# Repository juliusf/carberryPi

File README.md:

carberryPi
==========

1. Introduction
----------------

This project aims to build a linux-car pc based on the raspberry pi minicomputer.

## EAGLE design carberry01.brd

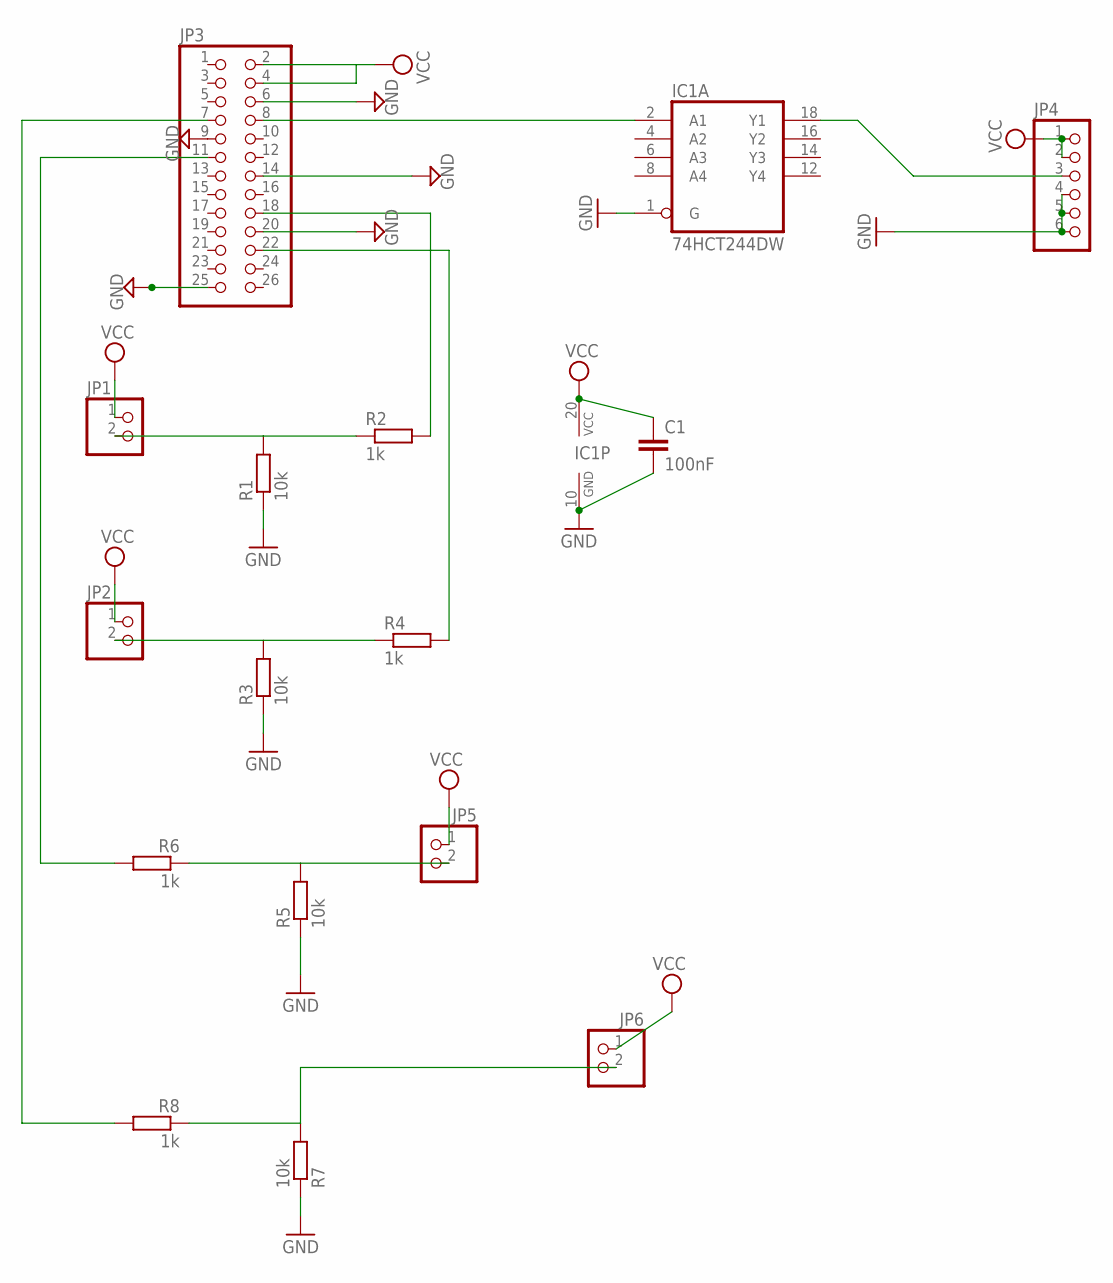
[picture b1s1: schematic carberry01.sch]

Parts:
C1: 100nF; C0603K
IC1: 74HCT244DW; SO20W
JP1, JP2, JP5, JP6: PINHD-1X2; 1X02
JP3: PINHD-2X13; 2X13
JP4: PINHD-1X6; 1X06
R1, R3, R5, R7: 10k; R0603
R2, R4, R6, R8: 1k; R0603

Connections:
GND: C1.2, IC1.1 (G), IC1.10 (GND), JP3.6, JP3.9, JP3.14, JP3.20, JP3.25, JP4.4, JP4.5, JP4.6, R1.1, R3.1, R5.1, R7.1
unnamed: IC1.18 (Y1), JP4.3
unnamed: JP1.2, R1.2, R2.1
unnamed: IC1.2 (A1), JP3.8
unnamed: JP2.2, R3.2, R4.1
unnamed: JP5.2, R5.2, R6.1
unnamed: JP6.2, R7.2, R8.1
unnamed: JP3.18, R2.2
unnamed: JP3.22, R4.2
unnamed: JP3.11, R6.2
unnamed: JP3.7, R8.2
VCC: C1.1, IC1.20 (VCC), JP1.1, JP2.1, JP3.2, JP3.4, JP4.1, JP4.2, JP5.1, JP6.1

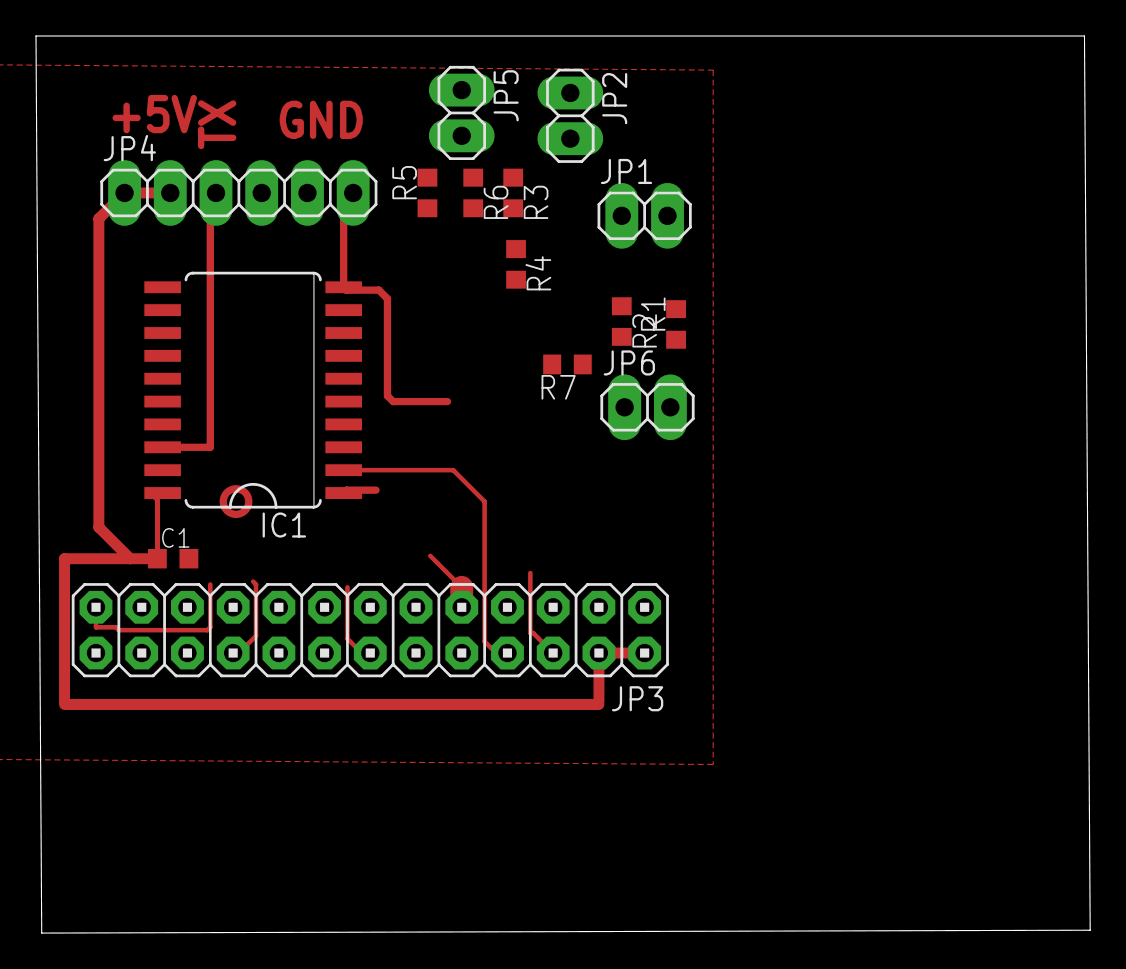
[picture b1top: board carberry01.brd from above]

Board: 2 copper layers, 58.6 x 49.8 mm, 16 parts (1 on the bottom side), 12 nets.

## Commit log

2013-02-13 inital commit of the gpio board
2013-02-13 completed routing of gpio board
2013-02-13 fixed file mess
